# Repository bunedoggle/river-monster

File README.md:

river-monster
=============

River monitoring hack-a-thon at the Lowell Makerspace.

Goals:
 - Battery-less sensors using energy havevesting
 - Sensor gateway using SMS
 - Solar gateway charging

###Update: 11/6/2014

As a first pass project we're going to change the remote sensor design.  Each sensor node will use an inexpensive 433Mhz transmitter module (like this) and an Arduino pro mini.  Using the low power library we shuold be able to get month of battery life from a few AA batteries, maybe longer with a lithium-ion.

The gateway will be an Arduino Uno with a GPRS sheild, 433 Mhz reciever and a large antenna.

This will greatly simplify the design and allow us to quickly build a proof on concept that can be expanded.

See the wiki for more info. 

Resources:
 - http://www.seeedstudio.com/depot/GPRS-Shield-V20-p-1379.html?cPath=132_134
 - http://publiclab.org/wiki/water-quality-sensor
 - https://www.enocean.com/en/enocean-pi/

Low Power Arduino lib:
 - http://www.rocketscream.com/blog/2011/07/04/lightweight-low-power-arduino-library/
 - https://github.com/rocketscream/Low-Power

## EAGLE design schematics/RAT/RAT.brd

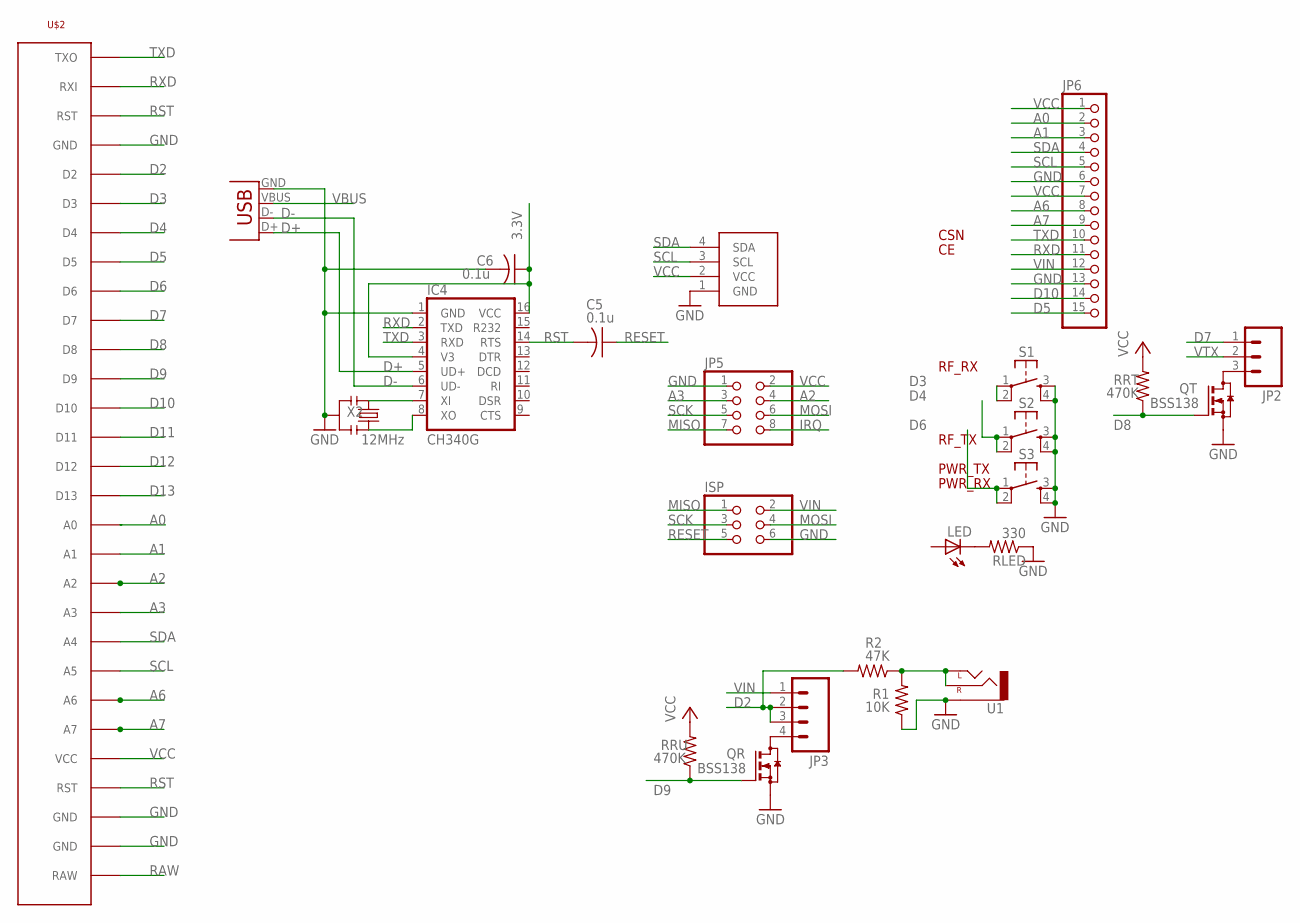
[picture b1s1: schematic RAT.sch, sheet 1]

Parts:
C5, C6: 0.1u; C0805K
IC4: CH340G; SO16
ISP: PINHD-2X3; 2X03
JP2: M03LOCK_LONGPADS; 1X03_LOCK_LONGPADS
JP3: M04LOCK; 1X04_LOCK
JP5: PINHD-2X4; 2X04
JP6: PINHD-1X15-CB; 1X15-CB
LED: LEDCHIPLED_0805; CHIPLED_0805
QR: BSS138; SOT23
QT: BSS138; SOT23
R1: 10K; R0805
R2: 47K; R0805
RLED: 330; R0805
RRT: 470K; R0805
RRU: 470K; R0805
S1, S2, S3: TAC_SWITCHPTH; TACTILE-PTH
U1: AUDIO-JACKPTH; AUDIO-JACK
U$1: SSD1306_OLED_I2C
U$2: ARDUINO-PRO-MINI-CORRECT; ARDUINO-PRO-MINI
X1: USBSMD; USB-MINIB
X2: 12MHz; RESONATOR-SMD

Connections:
3.3V: C6.1, IC4.4 (V3), IC4.16 (VCC)
A0: JP6.2, U$2.A0
A1: JP6.3, U$2.A1
A2: JP5.4, U$2.A2
A3: JP5.3, U$2.A3
A6: JP6.8, U$2.A6@1 (A6), U$2.A6@2 (A6)
A7: JP6.9, U$2.A7@1 (A7), U$2.A7@2 (A7)
D2: JP3.2, JP3.3, R2.2, U$2.2 (D2)
D3: S1.1, S1.2, U$2.3 (D3)
D4: S2.1, S2.2, U$2.4 (D4)
D5: JP6.15, U$2.5 (D5)
D6: S3.1, S3.2, U$2.6 (D6)
D7: JP2.1, U$2.7 (D7)
D8: QT.1 (G), RRT.1, U$2.8 (D8)
D9: QR.1 (G), RRU.1, U$2.9 (D9)
D10: JP6.14, U$2.10 (D10)
D11: U$2.11 (D11)
D12: U$2.12 (D12)
D13: U$2.13 (D13)
D+: IC4.5 (UD+), X1.D+
D-: IC4.6 (UD-), X1.D-
GND: C6.2, IC4.1 (GND), ISP.6, JP5.1, JP6.6, JP6.13, QR.2 (S), QT.2 (S), R1.1, RLED.1, S1.3, S1.4, S2.3, S2.4, S3.3, S3.4, U1.SLEEVE, U$1.1 (GND), U$2.GND@1 (GND), U$2.GND@2 (GND), U$2.GND@3 (GND), X1.GND, X2.2; also elsewhere on the board
IRQ: JP5.8
MISO: ISP.1, JP5.7
MOSI: ISP.4, JP5.6
unnamed: LED.C, RLED.2
unnamed: R1.2, R2.1, U1.RING (RIGHT), U1.TIP (LEFT)
unnamed: JP3.4, QR.3 (D)
unnamed: JP2.3, QT.3 (D)
unnamed: IC4.7 (XI), X2.1
unnamed: IC4.8 (XO), X2.3
RAW: U$2.RAW
RESET: C5.1, ISP.5
RST: C5.2, IC4.14 (RTS), U$2.RST@1 (RST), U$2.RST@2 (RST)
RXD: IC4.2 (TXD), JP6.11, U$2.RXI
SCK: ISP.3, JP5.5
SCL: JP6.5, U$1.3 (SCL), U$2.A5
SDA: JP6.4, U$1.4 (SDA), U$2.A4
TXD: IC4.3 (RXD), JP6.10, U$2.TXO
VBUS: X1.VBUS; also elsewhere on the board
VCC: JP5.2, JP6.1, JP6.7, RRT.2, RRU.2, U$1.2 (VCC), U$2.VCC; also elsewhere on the board
VIN: ISP.2, JP3.1, JP6.12
VTX: JP2.2; also elsewhere on the board

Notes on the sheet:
RF_RX
PWR_RX
PWR_TX
RF_TX
CSN

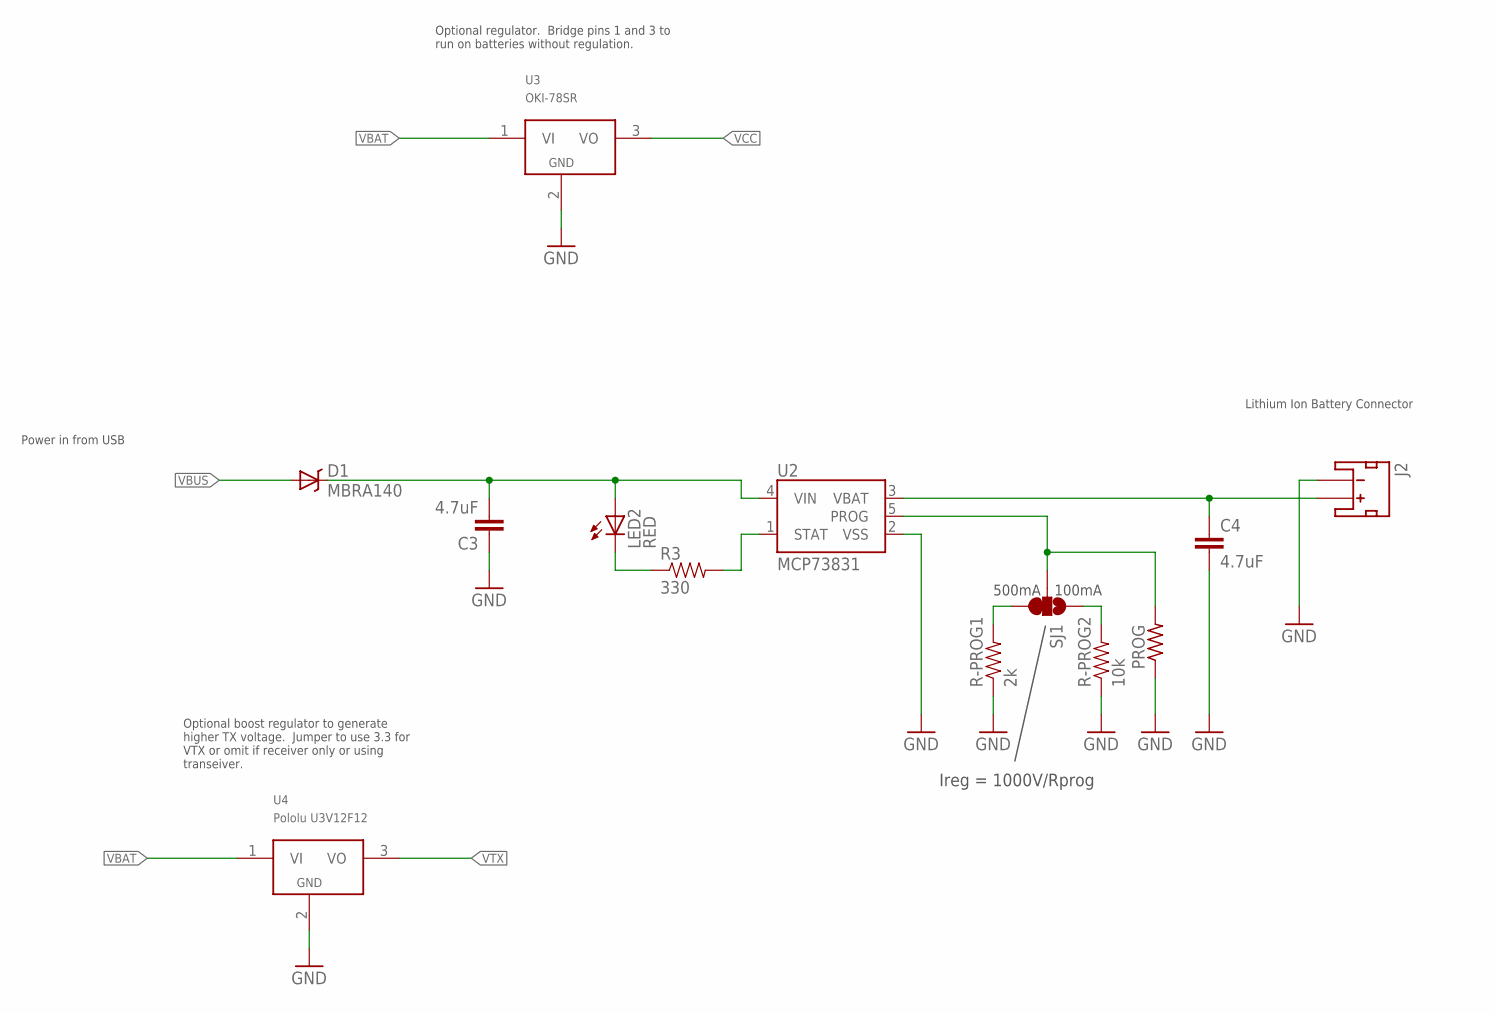
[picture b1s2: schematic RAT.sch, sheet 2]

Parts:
C3, C4: 4.7uF; 0603-CAP
D1: MBRA140; SMA-DIODE
J2: JST_2MM_MALE; JST-2-SMD
LED2: RED; LED-0603
PROG: R-US_R0603; R0603
R3: 330; 0603-RES
R-PROG1: 2k; 0603-RES
R-PROG2: 10k; 0603-RES
SJ1: SOLDERJUMPER_2WAYS; SJ_3
U2: MCP73831; SOT23-5
U3: OKI-78SR; TO-220
U4: Pololu U3V12F12; TO-220

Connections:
GND: C3.1, C4.2, J2.1 (-), PROG.1, R-PROG1.1, R-PROG2.1, U2.2 (VSS), U3.2 (GND), U4.2 (GND); also elsewhere on the board
unnamed: R-PROG1.2, SJ1.3
unnamed: R3.2, U2.1 (STAT)
unnamed: R-PROG2.2, SJ1.1
unnamed: LED2.C, R3.1
PROG: PROG.2, SJ1.2, U2.5 (PROG)
VBAT: C4.1, J2.2 (+), U2.3 (VBAT), U3.1 (VI), U4.1 (VI)
VBUS: D1.A; also elsewhere on the board
VBUS_DIODE: C3.2, D1.C, LED2.A, U2.4 (VIN)
VCC: U3.3 (VO); also elsewhere on the board
VTX: U4.3 (VO); also elsewhere on the board

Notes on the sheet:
500mA
100mA
Ireg = 1000V/Rprog
Optional regulator. Bridge pins 1 and 3 to run on batteries without regulation.
Lithium Ion Battery Connector
Power in from USB
Optional boost regulator to generate higher TX voltage. Jumper to use 3.3 for VTX or omit if receiver only or using transeiver.

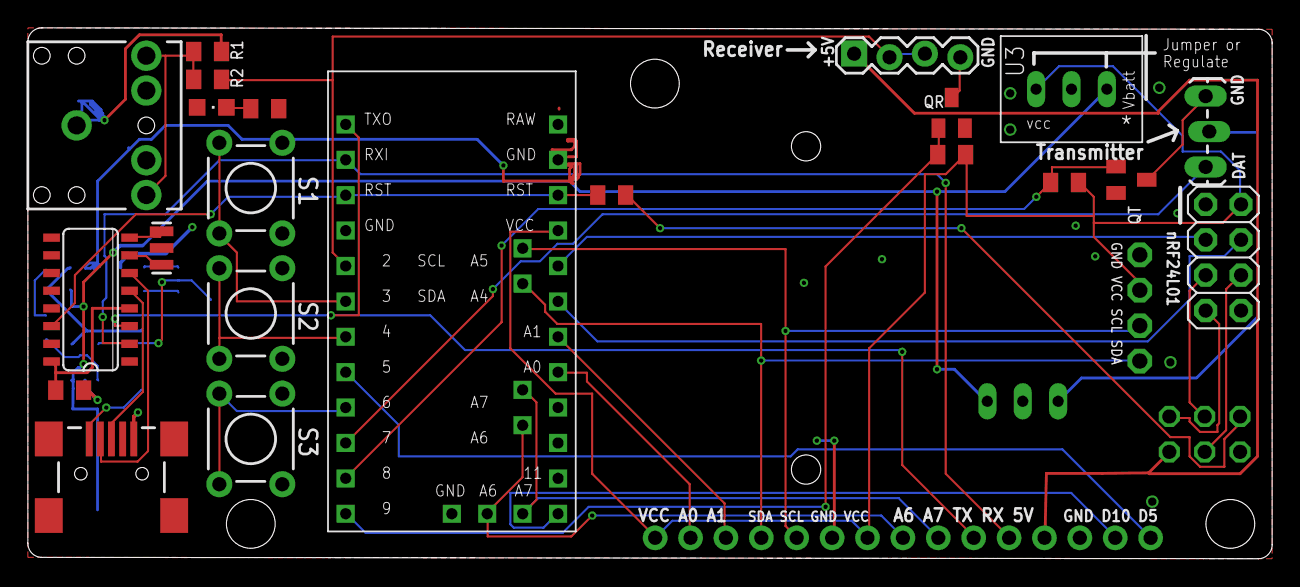
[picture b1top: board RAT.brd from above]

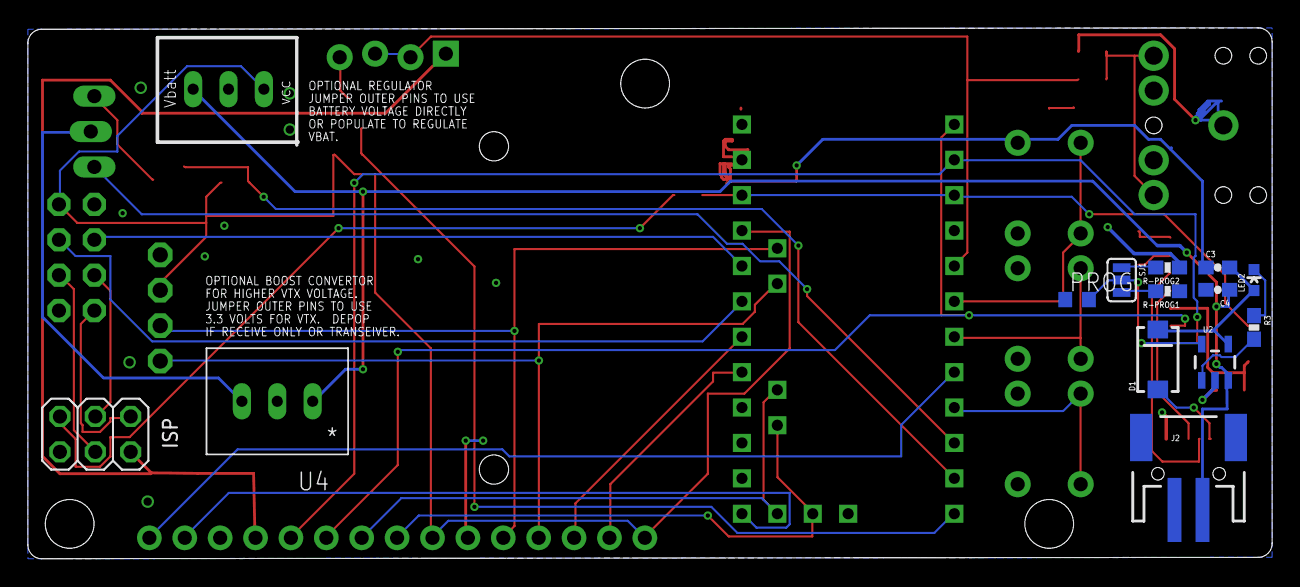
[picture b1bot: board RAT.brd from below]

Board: 2 copper layers, 89.3 x 38.1 mm, 37 parts (13 on the bottom side), 45 nets.

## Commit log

2014-10-23 Added some documentation
2014-10-27 Uppdate readme
2014-10-27 Added moore docs
2014-10-27 Added image
2014-10-27 Added image to readme
2014-10-28 Added low power arduino lib link
2014-10-28 Added Raspberry pi schematic to docs
2014-10-28 Added serial port example driver code
2014-10-29 Added EnOcean Link example code to connect rPi to EnOcean Pi module
2014-10-29 Pushing the STM 33X temp sensor users manual
2014-10-30 Initial commit of LockServer node project
2014-10-30 Added working Arduino GPRS shield example
2014-11-01 CSI files
2014-11-01 Added CSI example
2014-11-01 added serial port setting shell script
2014-11-01 Python script to open serial and send enocear data
2014-11-01 Implemented 'send text' command.
2014-11-02 tweaks to run.py
2014-11-02 fix typo
2014-11-05 Pushing a working xmit/rcv example that connects two arduinos via cheap 433mhz modules
2014-11-05 Added Turbidity transmission code
2014-11-05 Working transmitter, sleeps, 5.15 mA draw at idle. Measurements still a bit wonky
2014-11-06 Now receiving and decoding packets.
2014-11-07 Receive code now reading faily close turbidity and temperature values. Added attribute packed to data packet so it works.
2014-11-07 added wireing for sensor node
2014-11-07 added wireing for gateway
2014-11-08 Added time to low poer sleep. Power down sensor during xmit. Better calibration on recvr.
2014-11-11 Adding schematic and board layout. This was a first pass. I'm about to unroute the board and move all the components. this is a checkpoint

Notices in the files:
parts and their libraries:
SparkFun-PowerIC: Licensing: CC v3.0 Share-Alike You are welcome to use this library for commercial purposes.
